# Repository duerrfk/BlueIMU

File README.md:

# What is BlueIMU?

BlueIMU is an Inertial Measurement Unit (IMU) with 6 degrees of freedom and Bluetooth connectivity (serial port profile / SPP). 

The main features of BlueIMU are:

* Based on inexpensive, easily available hardware components, namely, the 6 degrees of freedom GY521 IMU module featuring an InvenSense MPU-6050 sensor, the HC06 Bluetooth module, and an Atmega328P microcontroller. 
* Runs from a single cell LiPo battery. An overdischarge protection is included in the design. 
* Raw sensor values can be transmitted at sampling rates of 200 Hz and higher through a 230400 Baud wireless serial connection (Bluetooth SPP).
* The BlueIMU software is based on the Arduino IDE and can be easily modified.
* Fully open source hardware (circuit board / PCB) and software design.
* Sample application with Kalman filter for calculating attitude (pitch and roll) included. 

The following image shows the BlueIMU board. The GY521 IMU module is the little blue board on the left; the green board is the HC06 Bluetooth module.

Note that BlueIMU uses a 6 degrees of freedom IMU with a 3 axes accelerometer and 3 axes gyroscope, but without a magnetometer (compass). This is sufficient for sensing the pitch and roll, for instance, for controlling the attitude of a drone. However, we cannot sense the yaw to navigate a drone. However, the design could be easily adapted to use a 9 degrees of freedom IMU such as the InvenSense MPU-9250 on the GY-9250 module (GY521 and GY-9250 both use I2C for connecting to the MCU, but the GY-9250 requires 10 instead of 8 header pins to connect to the BlueIMU board).
 
# Why Yet Another IMU?

Many wireless IMUs today are based on Bluetooth Low Energy (BLE). Although BLE is optimized for very low energy consumption, it lacks support for higher data rates and low latency as required by sensors at higher sampling rates. In particular, the minimum connection interval of 7.5 ms inherently limits the sampling rate of wireless BLE sensors to about 133 Hz, and together with the small frames of only 20 bytes payload, the data rate is limited. Therefore, BLE is a great technology if you strive for years of battery lifetime at moderate data rates, however, for higher data rates and sensor sampling rates, standard Bluetooth is the better choice.

Therefore, BlueIMU uses standard Bluetooth supporting higher data rates (230400 Baud serial connection) to allow for higher sensor sampling rates at 200 Hz and higher.

# Hardware Design

The design of the BlueIMU circuit board (PCB) can be found in folder `pcb` (Eagle schematics and board design as well as Gerber files for production at a PCB house are included). 
  
BlueIMU is based on easily available low-cost components such as the GY521 IMU featuring a 6 degrees of freedom (3x accelerometer, 3x gyroscope) InvenSense MPU-6050 sensor, a HC06 Bluetooth module, and an Atmega328P microcontroller (MCU), which is well-supported by the popular Arduino platform.

The following images shows the schematic of the BlueIMU board.

The Atmega328P MCU runs at 7.3728 MHz to allow for a perfect timing of the 230400 Baud serial connection to the HC06 Bluetooth module (230400 = 7.3728 MHz/32). Besides the serial connection, the HC06 module signals the Bluetooth connection state through a pin changing with a period of 750 ms while not connected and being constantly high while connected. Note that you need to porgram the HC06 module to use 230400 Baud using AT commands sent via the (wired) serial connection to the module (details can be found in the HC06 documentation).

A 6 pin connector is used to connect an in-system programmer with the following common pinout:

```
MISO <-- 1 2 --> VCC
SCK <--  3 4 --> MOSI
RST <--  5 6 --> GND
```

The GY521 module is connected through I2C to the MCU. It is soldered to the BlueIMU board using a 8 pin header providing for a rigid physical connection of the IMU to the BlueIMU board.

An overdischarge protection is included using the MAXIM ICL7665 voltage monitor. The MCU, IMU, and Bluetooth module will be disconnected from power at about 3.0 V. At about 3.3 V, the red LED (charge indicator) goes off to signal a low battery (the GY521 module has another onboard LED to show that the board is still running down to 3.0 V).  

## Preparing the Atmega328P (Programming Fuses)

Program the following fuses (note that "1" means fuse *not* programmed; "0" means fuse programmed):
  
* CKSEL = 1101, SUT 01: external crystal oscillator 3-8 MHz with fast startup times (BOD is enabled).
* CKDIV8 = 1: don't divide clock internally by 8.
* SPIEN = 0: enable serial programming.
* BODLEVEL = 101: brown-out detection set to 2.7 V.
* BOOTRST = 1: boot reset vector not enabled.
* RSTDISBL = 1: external reset not disabled.

This results in the following fuse bytes: 

* Low = 0xDD
* High = 0xD9
* Extended = 0x05

The MCU can be programmed using avrdude as follows:

```
$ sudo avrdude -c usbasp -p m328p -U lfuse:w:0xdd:m -U hfuse:w:0xd9:m -U efuse:w:0x05:m
```

## Flashing the Raw Transmitter Software

In folder `src/transmitter-raw` you find the raw transmitter software, which programs the BlueIMU to transmit raw measurements from the 3 axes accelerometer and 3 axes gyroscope of the MPU6050 IMU via Bluetooth serial profile (SPP). This software is implemented for the Arduino platform (tested with Arduino IDE 1.6.6) using the MPU6050 and I2C libraries by Jeff Rowberg.

In folder `arduino_board_definition` you find the corresponding board definition for the Atmega328P MCU running at 7.3728 MHz. Copy this directory into the folder `hardware` in your Arduino sketchbook.

Then, compile the Arduino sketch from folder `src/transmitter-raw`. This generates a hex file for the Atmega328P MCU. This hex file is a little bit hidden in the temporary build directory of the Arduino IDE. If you use Linux  and Arduino IDE 1.6, have a look at the `/tmp`  directory. After hitting the  compile button in the Arduino IDE, search for the latest hex file called  `transmitte-raw.cpp.hex` in a temporary directory named `/tmp/build...`. If you have found the hex file, you can flash it using avrdude:

```
$ sudo avrdude -p m328p -c usbasp -v -U flash:w:transmitter-raw.cpp.hex
```

## Data Format

Raw sensor data is transmitted over a Bluetooth serial connection. The transmitted data stream consists of records of the following format:

* Byte 0..1: Start of Record: 0x5A, 0xA5
* Byte 2..3: accelerometer X (16 bit signed int)  
* Byte 4..5: accelerometer Y (16 bit signed int)
* Byte 6..7: accelerometer Z (16 bit signed int)
* Byte 8..9: gyro X (16 bit signed int)
* Byte 10..11: gyro Y (16 bit signed int)
* Byte 12..13: gyro Z (16 bit signed int)
* Byte 14..17: sample time stamp (32 bit unsigned integer) in milliseconds since boot time
* Byte 18..19: 16 bit checksum

All 16 bit words are transmitted in Big Endian format (high byte first, low byte second). 

## Interpreting Raw Values

Values from sensors are transmitted as raw signed 16 bit values. The values can be translated to g and deg/s, respectively, depending on the configured sensor sensitivities (+-2g, +-4g, +-8g, +-16g; +-250 deg/s, +-500 deg/s, +- 1000 deg/s, +-2000 deg/s). The following resolutions are supported by the MPU6050 IMU:

* accelerometer: 16384, 8192, 4096, 2048 LSB / g
* gyro: 131, 65.5, 32.8, and 16.5 LSB / (deg/s) 

Please have a look at the manual of the MPU6050 for further details.

## Checksum 

The checksum consists of the ones' complement of the ones' complement sum of the 16-bit words, similar to the calculation of the checksum of IP headers. For detailed information on how to calculate the checksum, please have a look at the code. 

## Sampling Rate

The sampling rate can be adjusted by the SAMPLING_PERIOD definition.

## Low-pass Filter

The MPU 6050 features a low-pass filter. You can set the filter by defining DLPF according to the following table:

             |   ACCELEROMETER    |           GYROSCOPE
    DLPF_CFG | Bandwidth | Delay  | Bandwidth | Delay  | Sample Rate
    ---------+-----------+--------+-----------+--------+-------------
    0        | 260Hz     | 0ms    | 256Hz     | 0.98ms | 8kHz
    1        | 184Hz     | 2.0ms  | 188Hz     | 1.9ms  | 1kHz
    2        | 94Hz      | 3.0ms  | 98Hz      | 2.8ms  | 1kHz
    3        | 44Hz      | 4.9ms  | 42Hz      | 4.8ms  | 1kHz
    4        | 21Hz      | 8.5ms  | 20Hz      | 8.3ms  | 1kHz
    5        | 10Hz      | 13.8ms | 10Hz      | 13.4ms | 1kHz
    6        | 5Hz       | 19.0ms | 5Hz       | 18.6ms | 1kHz
    7        |   -- Reserved --   |   -- Reserved --   | Reserved

# Connecting a Linux Host to BlueIMU over Bluetooth

You can connect a Linux host to the BlueIMU board via Bluetooth as follows:

Step 1: Find the BlueIMU device 

```
$ hcitool scan
Scanning ...
	00:11:12:31:04:12	BlueIMU
```

Step 2: Pairing Linux host and BlueIMU device:

```
$ bluetooth-agent 1234 00:11:12:31:04:12
```

Step 3: Add device profile

```
$ sudo nano /etc/bluetooth/rfcomm.conf
```

Add the following section:

```
rfcomm1 {
  bind no;
  device 00:11:12:31:04:12;
  channel 1;
  comment "Blue IMU serial Port";
}
```

Connect host to BlueIMU device: 

```
$ rfcomm connect 1
```

Now, you should have a serial device called `/dev/rfcomm1` that you can open with your application. For instance, you can use screen to log data as follows:

```
$ screen -L /dev/rfcomm1
```

# Kalman Filter

In folder `src/receiver-attitude` you find a sample application for Linux implementing a Kalman filter to calculate the attitude (pitch and roll) and logging raw sensor values and Kalman filter values (pitch, roll, estimated gyro bias) to a file as comma-separate values. Note that the GY521 IMU does not feature a magnetometer (compass), thus, we cannot easily detect the absolute heading (yaw). 

You can compile this application with the following commands:

```
$ cd src/receiver-attitude
$ make 
```

Then you start it as follows:

```
$ ./receiver-attitude -d /dev/rfcomm1 -o out.csv
```

The Kalman filter uses the following equations:

State vector (phi is the angle; phidot is the angular velocity; bias is the bias of angular velocity (gyro bias)): 

```
    [ phi  ] 
x = [phidot]
    [ bias ] 
```

State equation:

```
x(k) = F(k)*x(k-1) + omega(k)
```

with

```
       [1 t_delta -t_delta]
F(k) = [0    1        0   ]
       [0    0        1   ]
```

This implementation assumes no control input model (B). Instead, a normally distributed random angular acceleration (phidotdot) is introduced modeling the effect of external forces like motors as part of the random process noise (omega):

```
           [t_delta**2/2]
omega(k) = [  t_delta   ] * phidotdot
           [     0      ]
```

Covariance matrix Q of normally distributed random process noise omega ~ N(0,Q):

```
Q = G*Gtrans*sigma_phidotdot**2 

    [t_delta**4/4  t_delta**3/2  0]                        [ 0 0 0 ]
  = [t_delta**3/2   t_delta**2   0] * sigma_phidotdot**2 + [ 0 0 0 ] * sigma_bias**2 
    [      0             0       0]                        [ 0 0 1 ]
```

Moreover, we assume that we can measure the angle from the IMU acceleration (phi_m) and the angular velocity (phidot_m) from the gyroscope. However, we cannot measure the gyro bias. Measurements are modeled as independent normally distributed random variables to account for measurement noise. The covariance matrix R of normally distributed random measuring noise v ~ N(0,R) is defined as:

```
    [sigma_phi_m**2         0         ]
R = 
    [     0          sigma_phidot_m**2]
```

Sample data of a stationary IMU and an IMU attached to a pendulum can be found in folder `sample-data`. 

The following plot shows the angle of a pendulum in radians over time as calculated by the Kalman filter:

As a comparison, here the angle in radians over time calculated directly from the accelerometer without Kalman filter, i.e., without fusing measurements from accelerometer and gyroscope:

Observer how the angle calculated just from acceleration is only correct while the object is at rest and clearly wrong when the pendulum moves such that gravity cannot be easily distinguished anymore from the acceleration caused by centripetal force. In that case, the Kalman filter can use the angular velocity to predict the angle leading to much more accurate results.

# License

The BlueIMU software (contents of folders `src`) is licensed under the Apache License, Version 2.0.

The BlueIMU hardware documentation (contents of folder `pcb`) is licensed under the CERN Open Hardware Licence, Version 1.2

Both licenses are included in the repository in the files `LICENSE-SOFTWARE` and `LICENSE-HARDWARE`, respectively.

The BlueIMU software uses the I2Cdev device library and MPU-6050 code by Jeff Rowberg licensed under the MIT license.

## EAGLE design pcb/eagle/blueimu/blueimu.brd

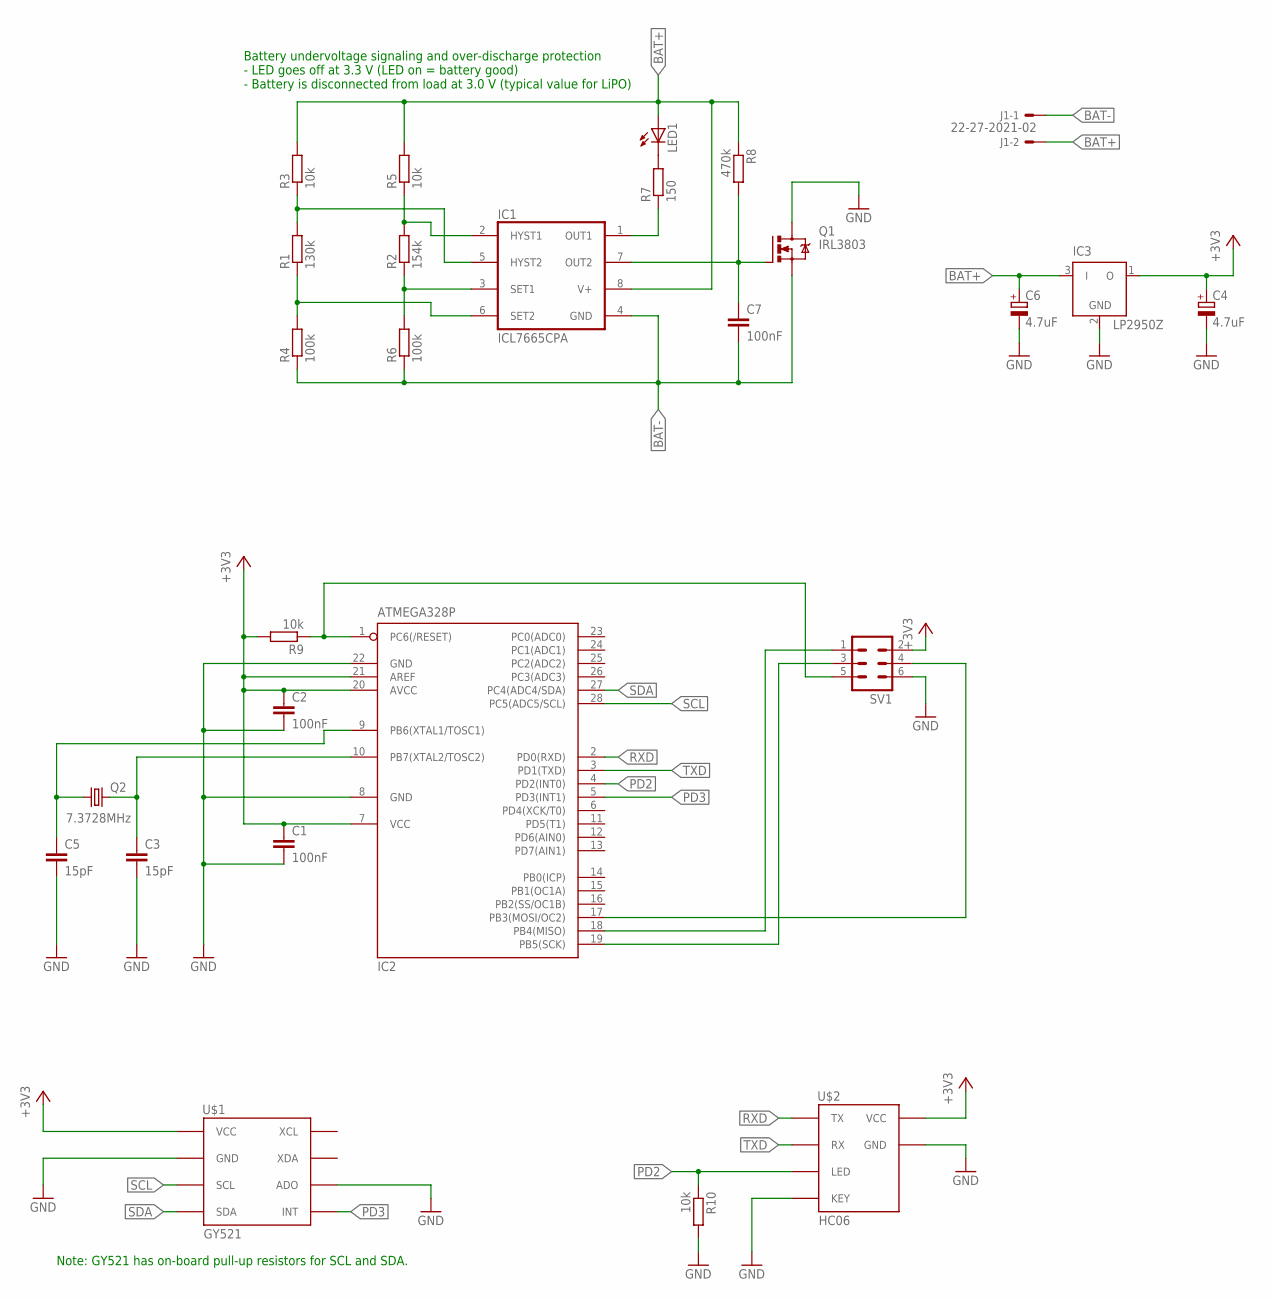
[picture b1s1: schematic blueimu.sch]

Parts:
C1, C2, C7: 100nF; C050-024X044
C3, C5: 15pF; C025-025X050
C4, C6: 4.7uF; E2,5-5
IC1: ICL7665CPA; DIL08
IC2: ATMEGA328P; DIL28-3
IC3: LP2950Z; TO92
J1: 22-27-2021-02; 6410-02
LED1: LED3MM
Q1: IRL3803; TO220BV
Q2: 7.3728MHz; HC49U-V
R1: 130k; 0207/7
R2: 154k; 0207/7
R3, R5, R9, R10: 10k; 0207/7
R4, R6: 100k; 0207/7
R7: 150; 0207/7
R8: 470k; 0207/7
SV1: MA03-2
U$1: GY521
U$2: HC06

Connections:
+3V3: C1.1, C2.1, C4.+, IC2.7 (VCC), IC2.20 (AVCC), IC2.21 (AREF), IC3.1 (O), R9.2, SV1.2, U$1.VCC, U$2.VCC
BAT+: C6.+, IC1.8 (V+), IC3.3 (I), J1.2, LED1.A, R3.2, R5.2, R8.1
BAT-: C7.2, IC1.4 (GND), J1.1, Q1.S, R4.1, R6.1
GND: C1.2, C2.2, C3.2, C4.-, C5.2, C6.-, IC2.8 (GND), IC2.22 (GND), IC3.2 (GND), Q1.D, R10.2, SV1.6, U$1.ADO, U$1.GND, U$2.GND, U$2.KEY
unnamed: LED1.K (C), R7.2
unnamed: IC1.1 (OUT1), R7.1
unnamed: IC1.2 (HYST1), R2.2, R5.1
unnamed: IC1.3 (SET1), R2.1, R6.2
unnamed: IC2.18 (PB4(MISO)), SV1.1
unnamed: IC2.19 (PB5(SCK)), SV1.3
unnamed: IC2.17 (PB3(MOSI/OC2)), SV1.4
unnamed: IC2.1 (PC6(/RESET)), R9.1, SV1.5
unnamed: C7.1, IC1.7 (OUT2), Q1.G, R8.2
unnamed: C3.1, IC2.10 (PB7(XTAL2/TOSC2)), Q2.2
unnamed: IC1.6 (SET2), R1.1, R4.2
unnamed: IC1.5 (HYST2), R1.2, R3.1
unnamed: C5.1, IC2.9 (PB6(XTAL1/TOSC1)), Q2.1
PD2: IC2.4 (PD2(INT0)), R10.1, U$2.LED
PD3: IC2.5 (PD3(INT1)), U$1.INT
RXD: IC2.2 (PD0(RXD)), U$2.TX
SCL: IC2.28 (PC5(ADC5/SCL)), U$1.SCL
SDA: IC2.27 (PC4(ADC4/SDA)), U$1.SDA
TXD: IC2.3 (PD1(TXD)), U$2.RX

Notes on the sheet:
Note: GY521 has on-board pull-up resistors for SCL and SDA.
Battery undervoltage signaling and over-discharge protection - LED goes off at 3.3 V (LED on = battery good) - Battery is disconnected from load at 3.0 V (typical value for LiPO)

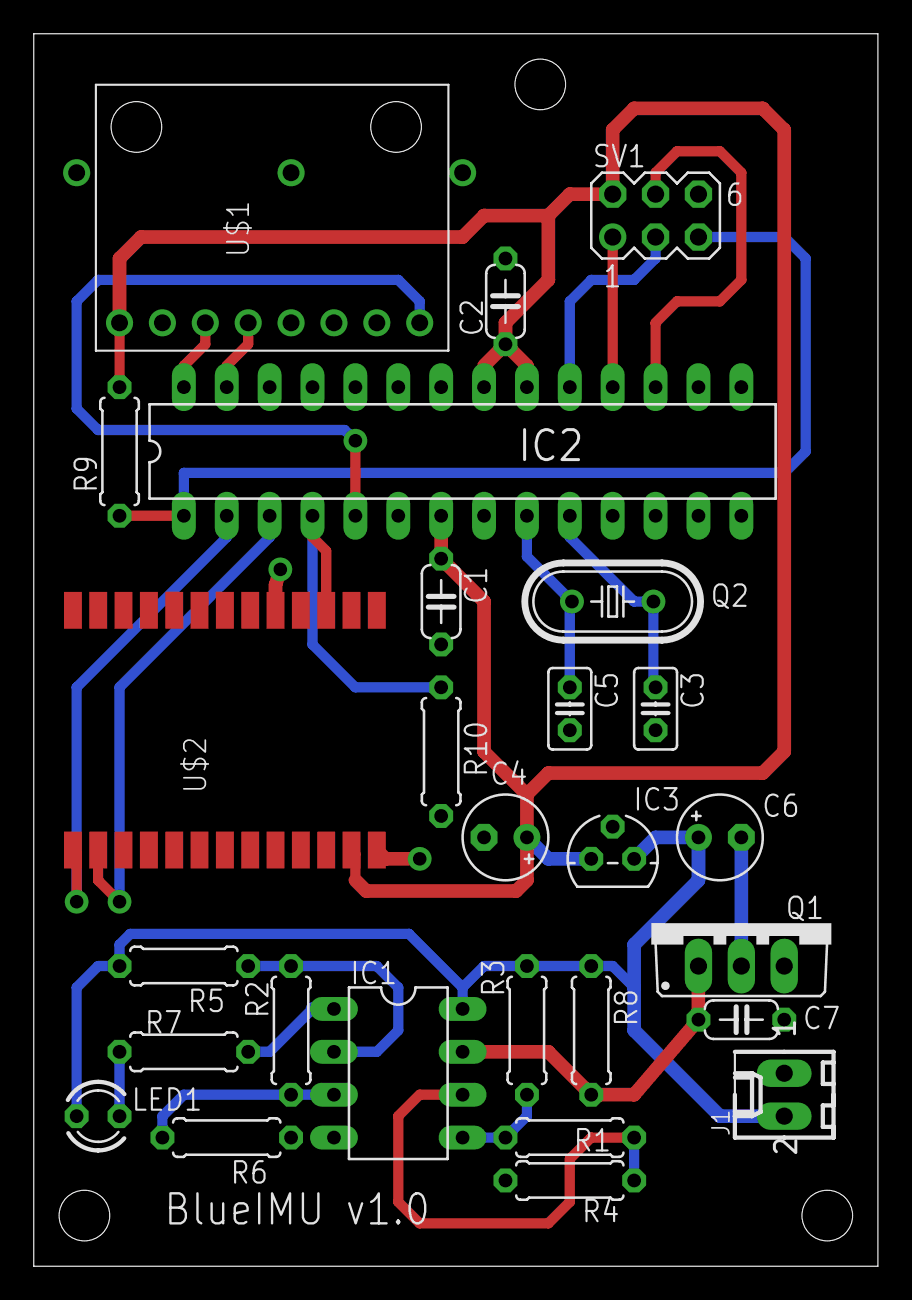
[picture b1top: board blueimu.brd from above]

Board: 2 copper layers, 50.0 x 73.0 mm, 27 parts (0 on the bottom side), 23 nets.

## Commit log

2016-04-10 Initial check-in
2016-04-11 Removed unnecessary pull-up resistor from serial line. Added pull-down resistor for LED output.
2016-04-11 Cosmetic label changes.
2016-05-15 Cosmetic changes to schematics and board layout
2016-05-26 Added capacitor. Added Gerber files.
2016-06-12 Added stub of transmitter implementation
2016-06-12 Added copyright notice. Added MPU6050 driver files.
2016-06-12 Added timestamps to samples. Added readme for raw-transmitter.
2016-06-12 Fixed bug in frame generation
2016-06-13 Added board definition
2016-06-13 Added notes
2016-06-19 Renamed transmitter. Added code for receiver.
2016-06-20 Added receiver code
2016-06-25 Fixed bugs in serial communication and checksum transmission. Added DEBUG flag.
2016-06-27 Added sensitivity
2016-07-10 Kalman filter now also estimating gyro bias
2016-07-11 Small changes
2016-08-24 Renamed receiver-orientation to receiver-attitude
2016-08-27 First working version of Kalman filter
2016-08-27 Added data from pendulum experiment
2016-12-27 Added images, sample data, and extended README.
2016-12-27 Extended Readme.
2016-12-27 Extended readme
2016-12-27 Merged readme files
2016-12-27 Revised readme
2016-12-28 Added image. Revised README.
2016-12-28 Final revision of readme.
2016-12-28 Added plot for gyro bias estimation.
